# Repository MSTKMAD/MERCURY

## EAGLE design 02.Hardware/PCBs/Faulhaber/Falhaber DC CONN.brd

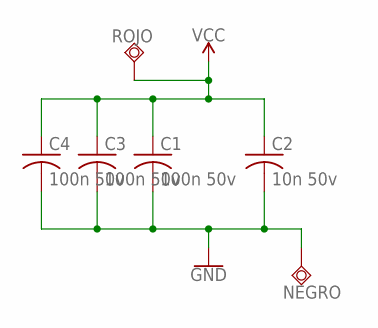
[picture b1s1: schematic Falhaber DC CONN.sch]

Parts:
C1, C3, C4: 100n 50v; C0805
C2: 10n 50v; C0805
NEGRO: TESTPAD_TPSQTP10SQ; TESTPAD_TP10SQ
ROJO: TESTPAD_TPSQTP10SQ; TESTPAD_TP10SQ

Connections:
GND: C1.2, C2.2, C3.2, C4.2, NEGRO.TP
VCC: C1.1, C2.1, C3.1, C4.1, ROJO.TP

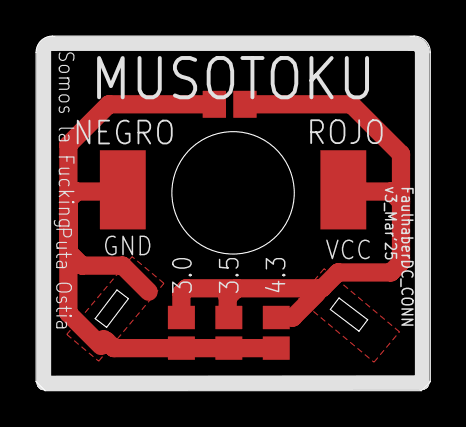
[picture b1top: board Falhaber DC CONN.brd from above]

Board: 2 copper layers, 21.9 x 19.7 mm, 6 parts (0 on the bottom side), 2 nets.

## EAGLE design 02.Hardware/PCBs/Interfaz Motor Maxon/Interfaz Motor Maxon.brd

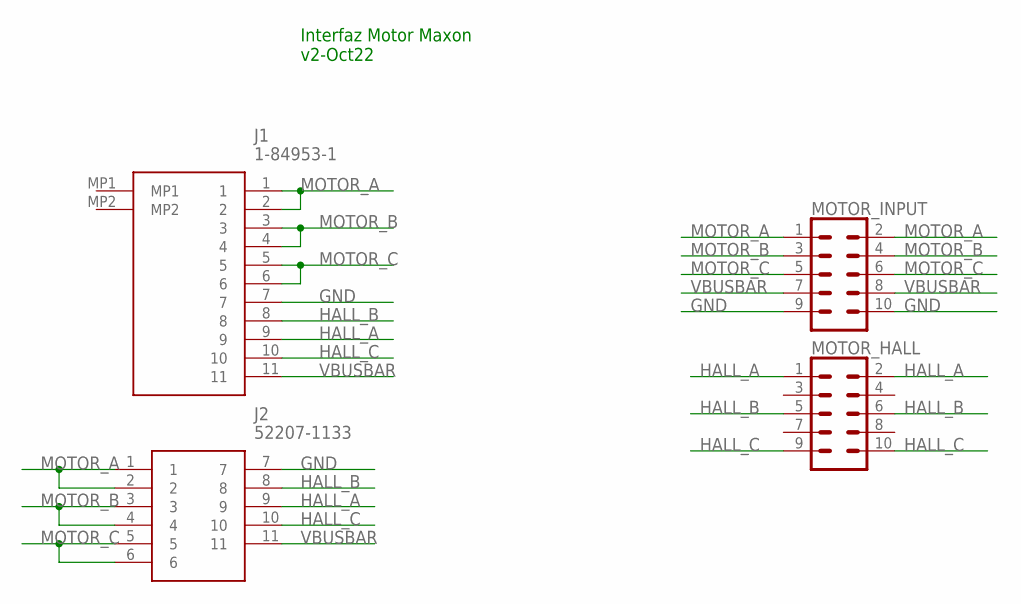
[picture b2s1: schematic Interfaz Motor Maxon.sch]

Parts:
J1: 1-84953-1; 1849531
J2: 52207-1133
MOTOR_HALL: CONN_05X2PTH; 2X5
MOTOR_INPUT: CONN_05X2PTH; 2X5

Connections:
GND: J1.7, J2.7, MOTOR_INPUT.9, MOTOR_INPUT.10
HALL_A: J1.9, J2.9, MOTOR_HALL.1, MOTOR_HALL.2
HALL_B: J1.8, J2.8, MOTOR_HALL.5, MOTOR_HALL.6
HALL_C: J1.10, J2.10, MOTOR_HALL.9, MOTOR_HALL.10
MOTOR_A: J1.1, J1.2, J2.1, J2.2, MOTOR_INPUT.1, MOTOR_INPUT.2
MOTOR_B: J1.3, J1.4, J2.3, J2.4, MOTOR_INPUT.3, MOTOR_INPUT.4
MOTOR_C: J1.5, J1.6, J2.5, J2.6, MOTOR_INPUT.5, MOTOR_INPUT.6
VBUSBAR: J1.11, J2.11, MOTOR_INPUT.7, MOTOR_INPUT.8

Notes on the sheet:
Interfaz Motor Maxon v2-Oct22

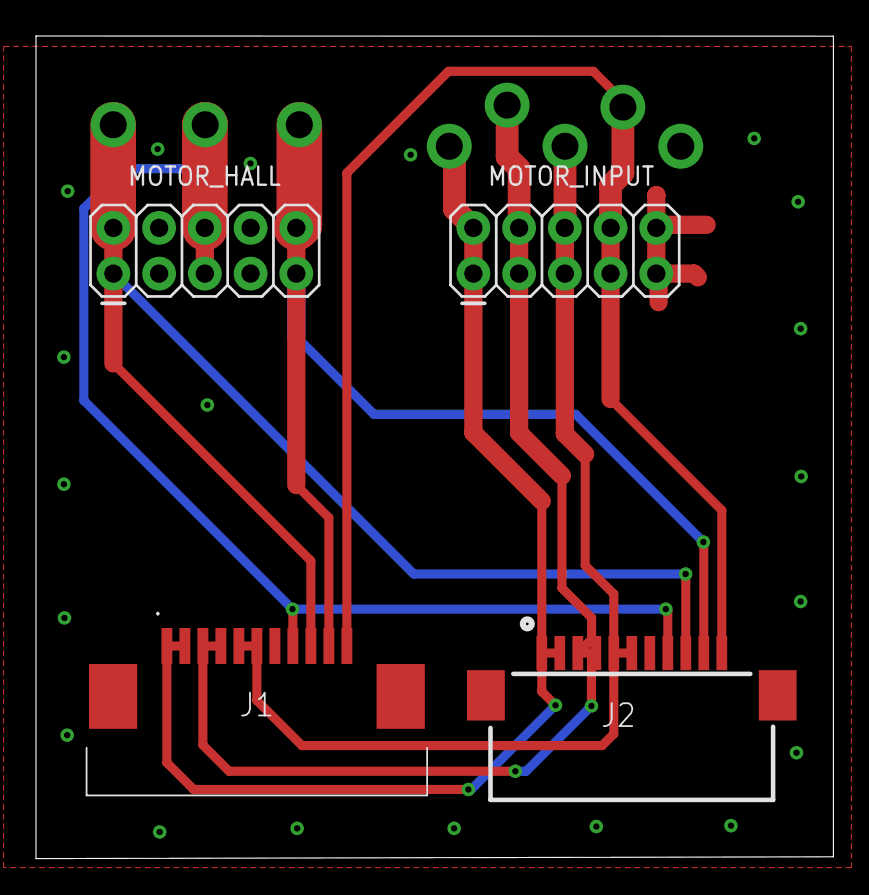
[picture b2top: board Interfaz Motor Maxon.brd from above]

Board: 2 copper layers, 44.3 x 45.7 mm, 4 parts (0 on the bottom side), 8 nets.

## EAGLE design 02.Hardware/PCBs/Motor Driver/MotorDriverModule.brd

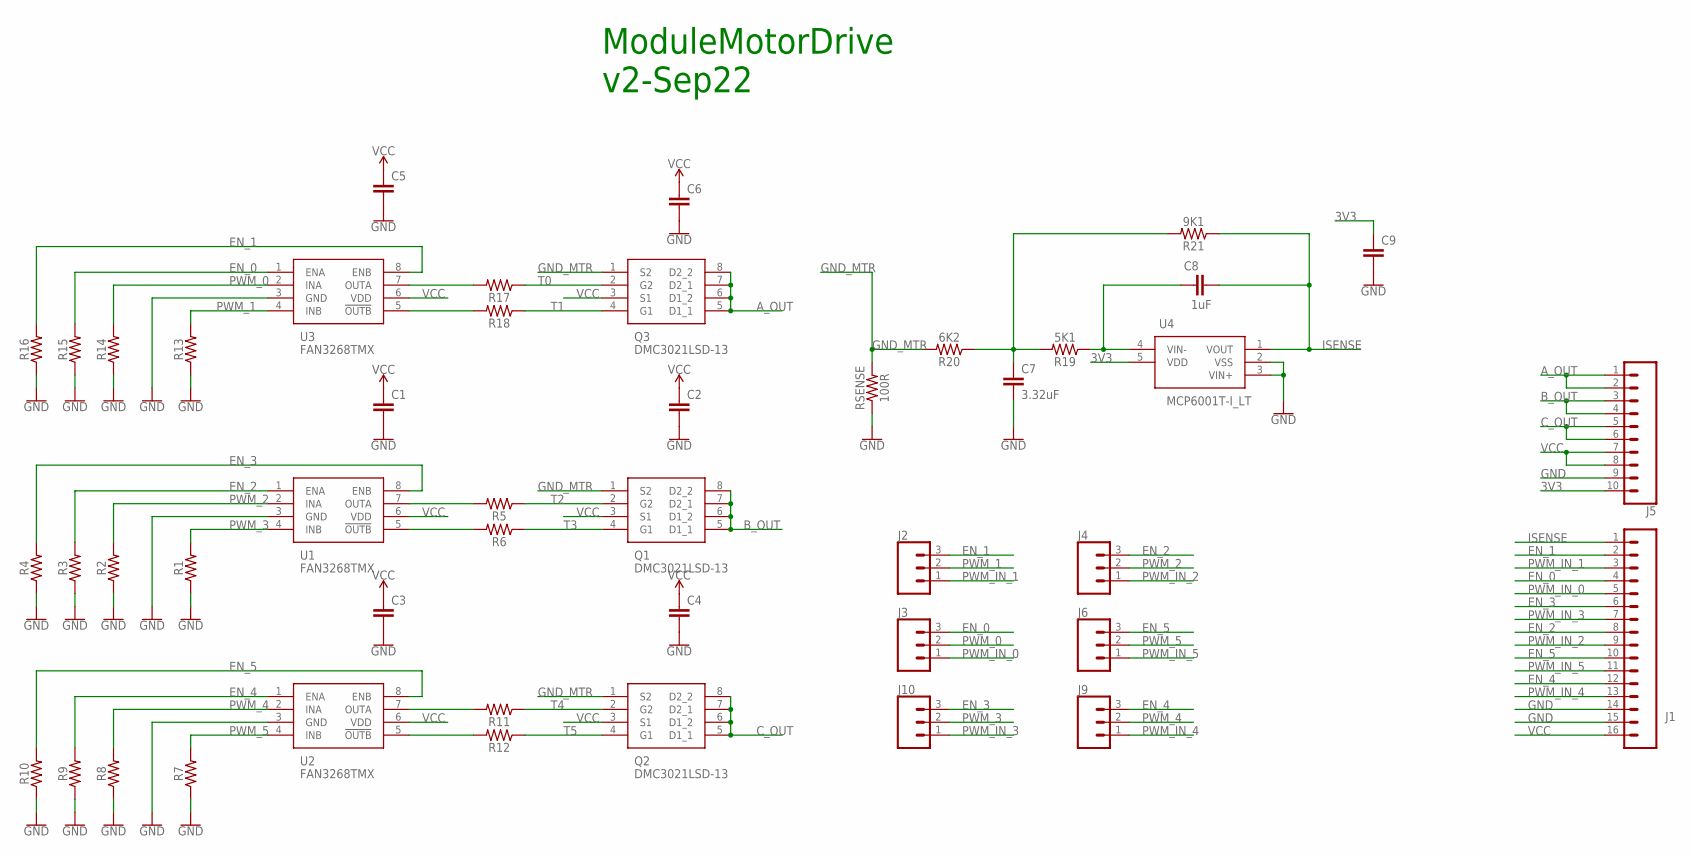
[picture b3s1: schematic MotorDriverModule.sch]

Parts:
C1, C2, C3, C4, C5, C6, C9: C-EUC0805; C0805
C7: 3.32uF; C0805
C8: 1uF; C0805
J1: CONN_16; 1X16
J2, J3, J4, J6, J9, J10: CONN_03; 1X03
J5: CONN_10"; 1X10
Q1, Q2, Q3: DMC3021LSD-13; SOIC127P600X175-8N
R1, R2, R3, R4, R5, R6, R7, R8, R9, R10, R11, R12, R13, R14, R15, R16, R17, R18: 0805
R19: 5K1; 0805
R20: 6K2; 0805
R21: 9K1; 0805
RSENSE: 100R; 1206
U1, U2, U3: FAN3268TMX; SOIC127P600X175-8N
U4: MCP6001T-I_LT; SOT65P210X110-5N

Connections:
3V3: C9.1, J5.10, U4.5 (VDD)
A_OUT: J5.1, J5.2, Q3.5 (D1_1), Q3.6 (D1_2), Q3.7 (D2_1), Q3.8 (D2_2)
B_OUT: J5.3, J5.4, Q1.5 (D1_1), Q1.6 (D1_2), Q1.7 (D2_1), Q1.8 (D2_2)
C_OUT: J5.5, J5.6, Q2.5 (D1_1), Q2.6 (D1_2), Q2.7 (D2_1), Q2.8 (D2_2)
EN_0: J1.4, J3.3, R15.2, U3.1 (ENA)
EN_1: J1.2, J2.3, R16.2, U3.8 (ENB)
EN_2: J1.8, J4.3, R3.2, U1.1 (ENA)
EN_3: J1.6, J10.3, R4.2, U1.8 (ENB)
EN_4: J1.12, J9.3, R9.2, U2.1 (ENA)
EN_5: J1.10, J6.3, R10.2, U2.8 (ENB)
GND: C1.2, C2.2, C3.2, C4.2, C5.2, C6.2, C7.2, C9.2, J1.14, J1.15, J5.9, R1.1, R2.1, R3.1, R4.1, R7.1, R8.1, R9.1, R10.1, R13.1, R14.1, R15.1, R16.1, RSENSE.1, U1.3 (GND), U2.3 (GND), U3.3 (GND), U4.2 (VSS), U4.3 (VIN+)
GND_MTR: Q1.1 (S2), Q2.1 (S2), Q3.1 (S2), R20.2, RSENSE.2
ISENSE: C8.2, J1.1, R21.1, U4.1 (VOUT)
unnamed: C7.1, R19.2, R20.1, R21.2
unnamed: C8.1, R19.1, U4.4 (VIN-)
unnamed: R6.2, U1.5 (!OUTB)
unnamed: R5.2, U1.7 (OUTA)
unnamed: R12.2, U2.5 (!OUTB)
unnamed: R11.2, U2.7 (OUTA)
unnamed: R18.2, U3.5 (!OUTB)
unnamed: R17.2, U3.7 (OUTA)
PWM_0: J3.2, R14.2, U3.2 (INA)
PWM_1: J2.2, R13.2, U3.4 (INB)
PWM_2: J4.2, R2.2, U1.2 (INA)
PWM_3: J10.2, R1.2, U1.4 (INB)
PWM_4: J9.2, R8.2, U2.2 (INA)
PWM_5: J6.2, R7.2, U2.4 (INB)
PWM_IN_0: J1.5, J3.1
PWM_IN_1: J1.3, J2.1
PWM_IN_2: J1.9, J4.1
PWM_IN_3: J1.7, J10.1
PWM_IN_4: J1.13, J9.1
PWM_IN_5: J1.11, J6.1
T0: Q3.2 (G2), R17.1
T1: Q3.4 (G1), R18.1
T2: Q1.2 (G2), R5.1
T3: Q1.4 (G1), R6.1
T4: Q2.2 (G2), R11.1
T5: Q2.4 (G1), R12.1
VCC: C1.1, C2.1, C3.1, C4.1, C5.1, C6.1, J1.16, J5.7, J5.8, Q1.3 (S1), Q2.3 (S1), Q3.3 (S1), U1.6 (VDD), U2.6 (VDD), U3.6 (VDD)

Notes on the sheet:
ModuleMotorDrive v2-Sep22

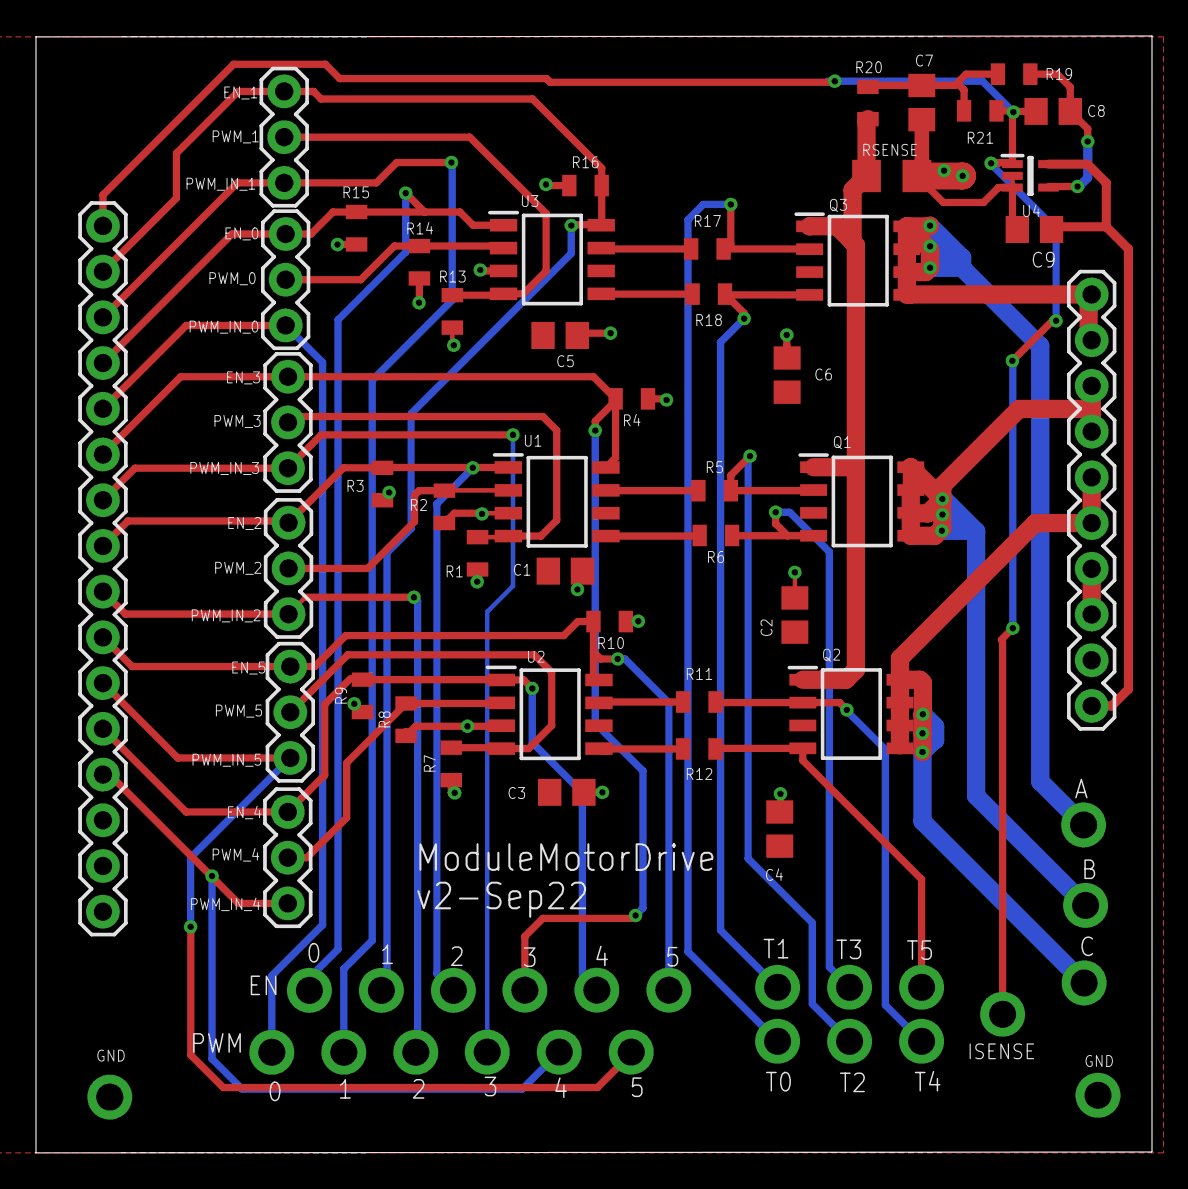
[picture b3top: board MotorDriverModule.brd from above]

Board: 2 copper layers, 62.0 x 62.0 mm, 46 parts (0 on the bottom side), 40 nets.

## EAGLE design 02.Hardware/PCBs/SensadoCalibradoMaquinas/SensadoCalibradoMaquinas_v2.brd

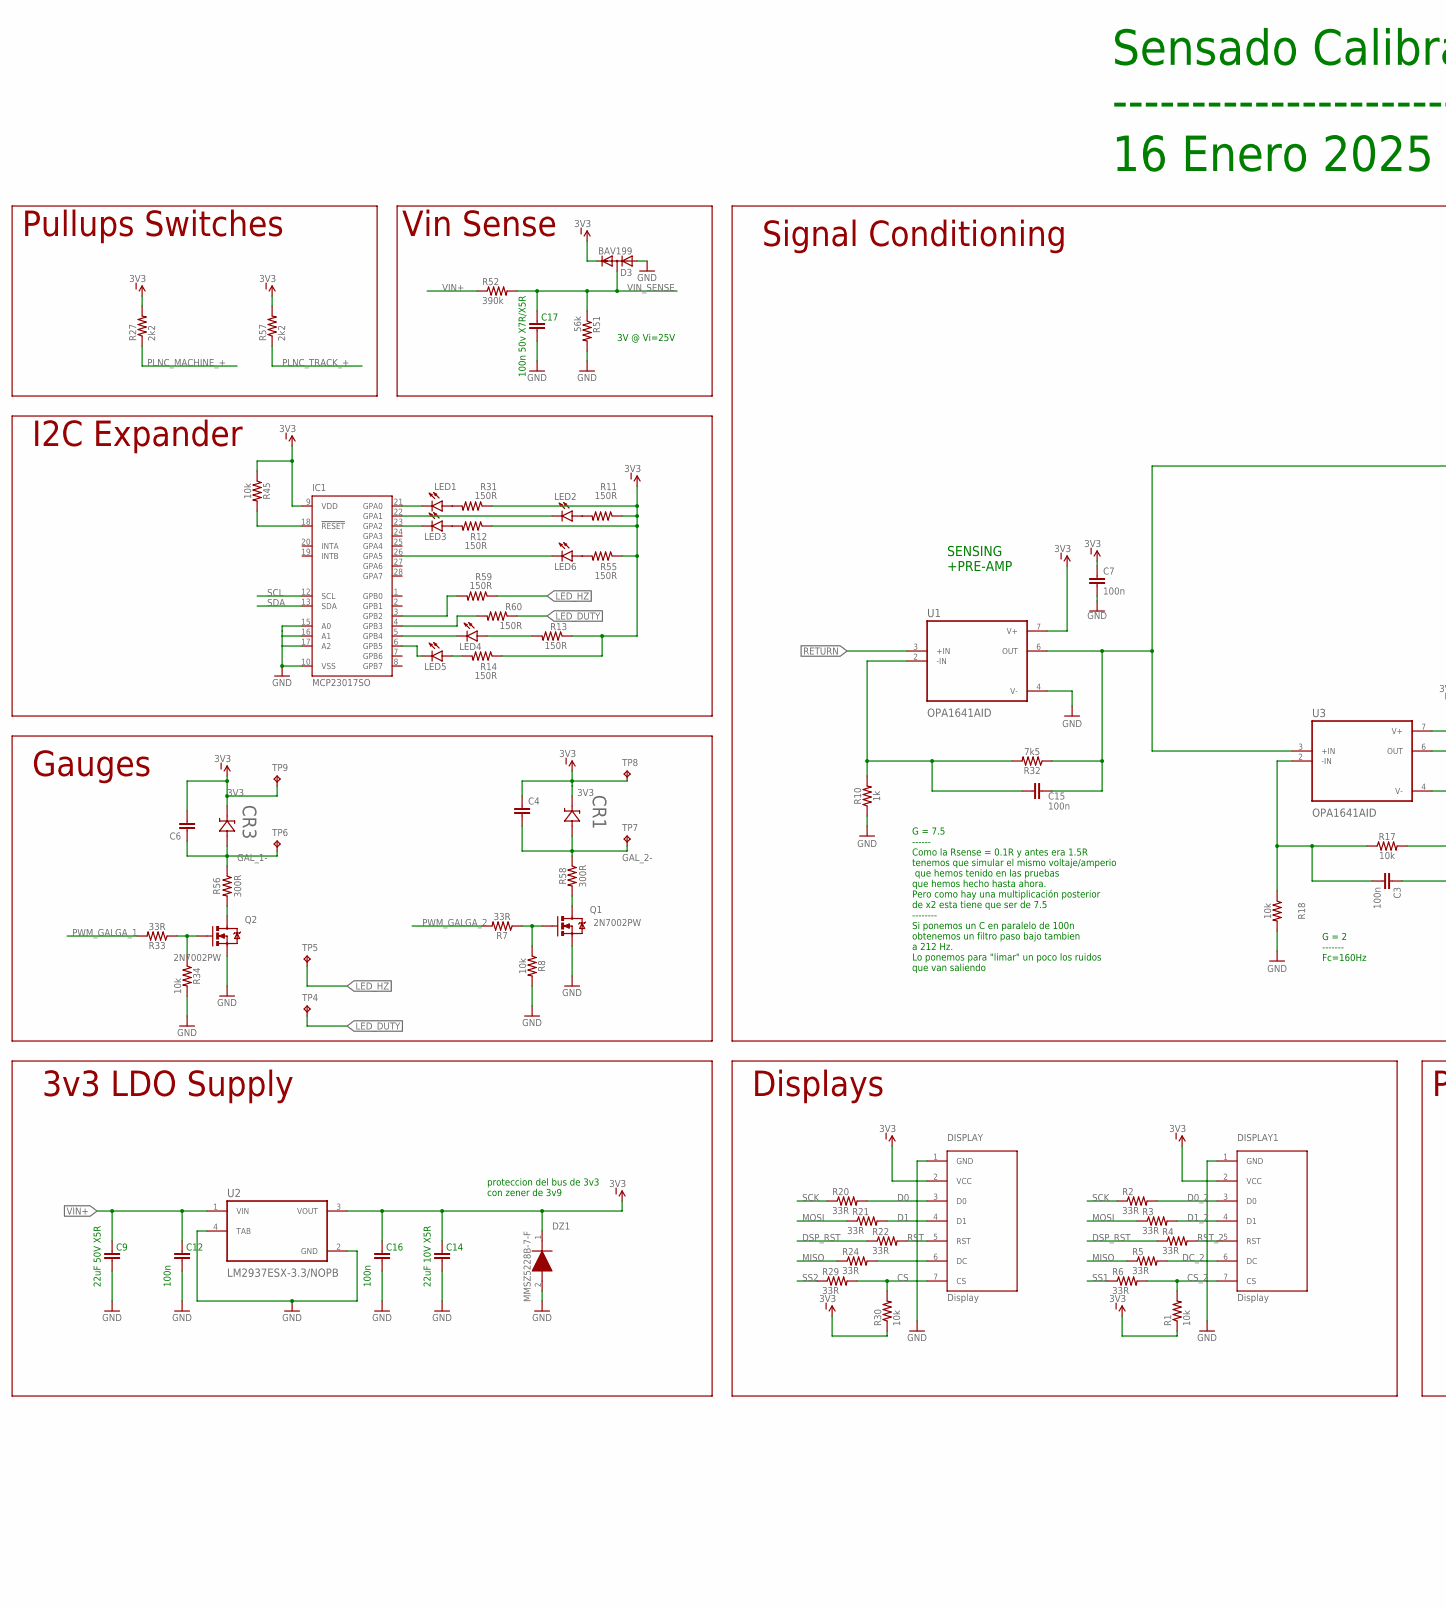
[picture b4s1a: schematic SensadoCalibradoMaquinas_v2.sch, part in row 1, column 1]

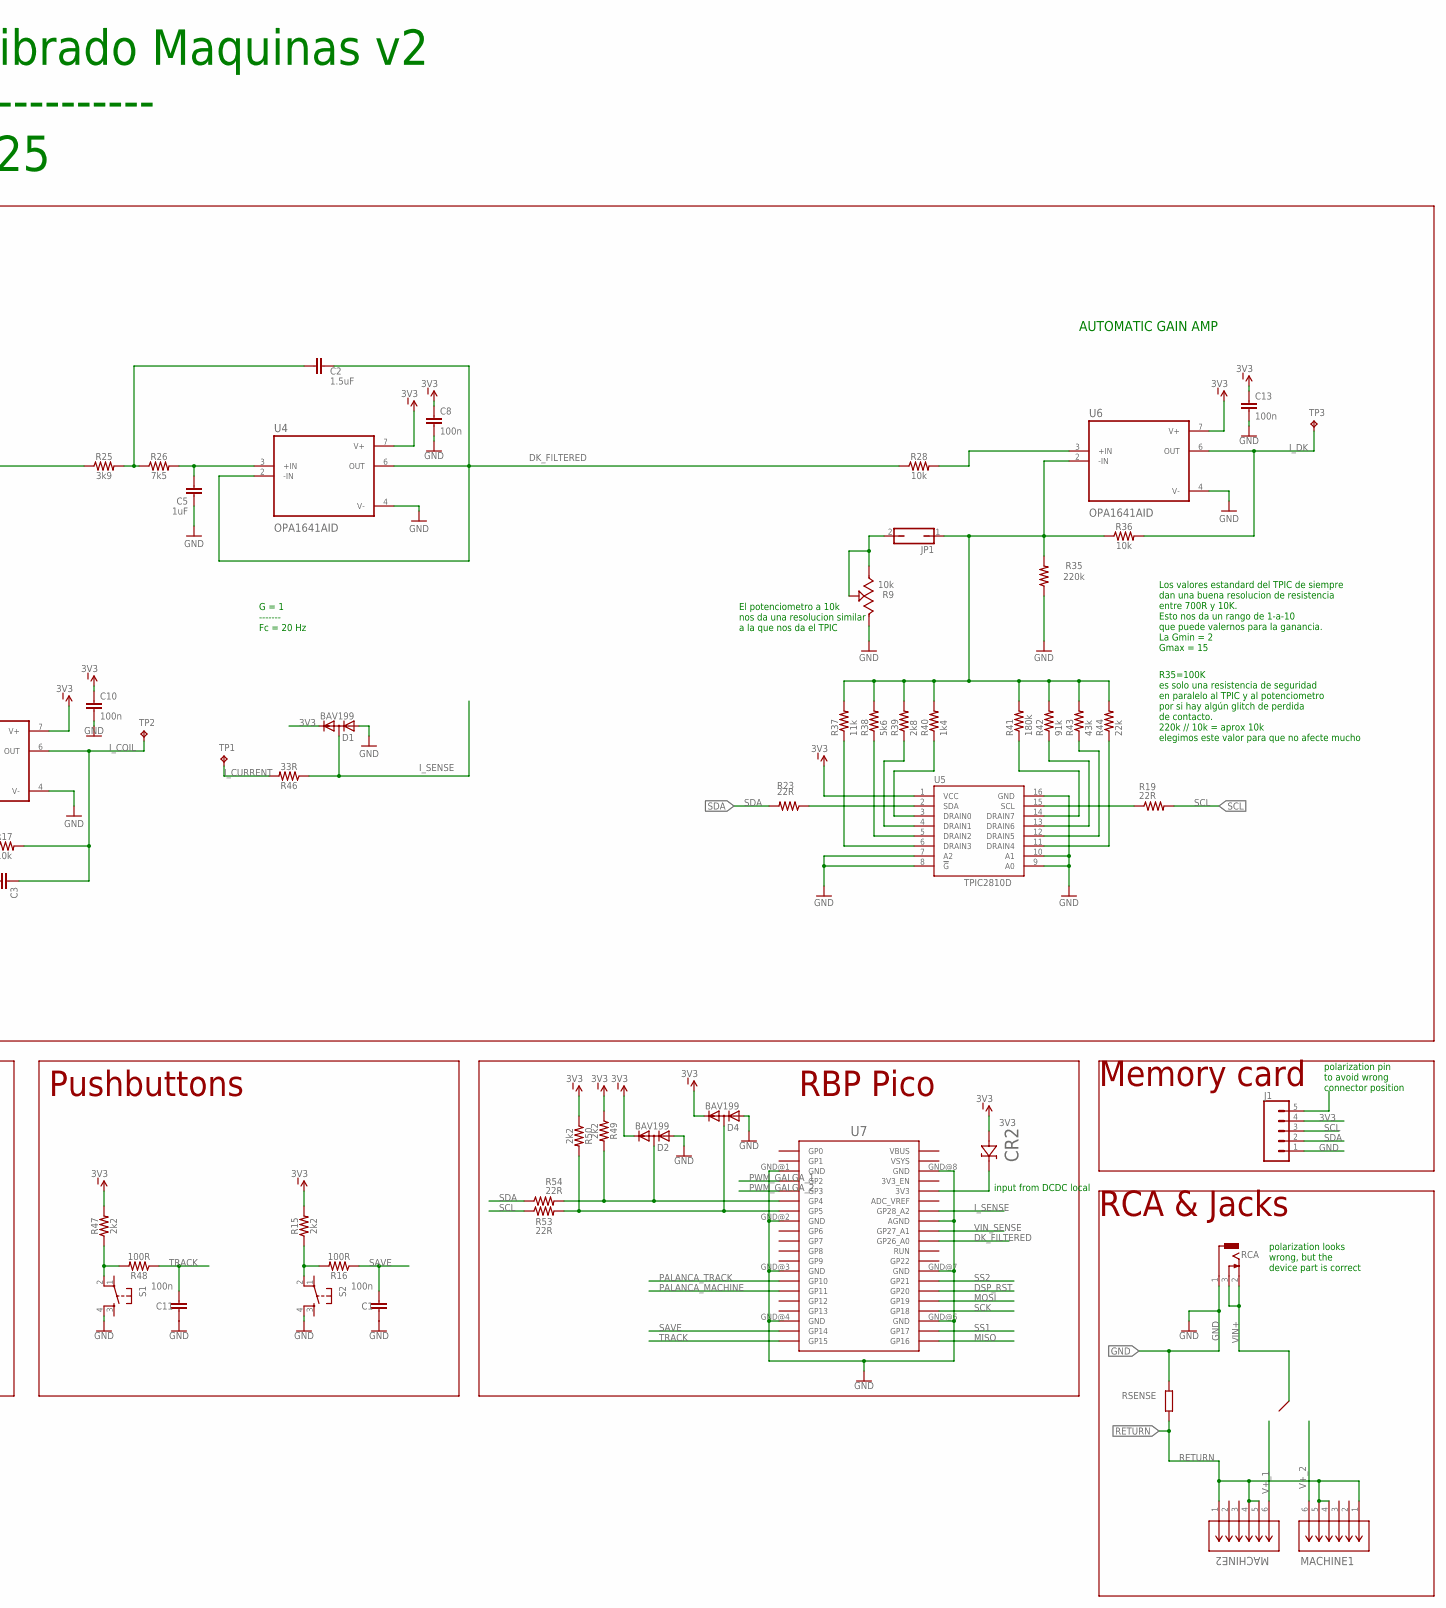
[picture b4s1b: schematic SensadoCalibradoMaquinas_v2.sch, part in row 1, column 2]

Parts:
C1, C3, C7, C8, C10, C11, C12, C13, C15, C16: 100n; 0805
C2: 1.5uF; 0805
C4, C6: CAP0805; 0805
C5: 1uF; 0805
C9: 22uF 50V X5R; 0805
C14: 22uF 10V X5R; 0805
C17: 100n 50v X7R/X5R; 0805
CR1, CR2, CR3: STPS1L40U; SMB_STM
D1, D2, D3, D4: BAV199; SOT23
DISPLAY, DISPLAY1: Display; OLED_LCD
DZ1: MMSZ5228B-7-F; SODFL3518X115N
IC1: MCP23017SO; SO28W
J1: CONN_05; 1X05
JP1: JP1Q; JP1
LED1, LED2, LED3, LED4, LED5, LED6: LED3MM
MACHINE1, MACHINE2: ACJS-MHDR; CONN_MHDR_AMP
Q1, Q2: 2N7002PW; SOT323
R1, R8, R17, R18, R28, R30, R34, R36, R45: 10k; 0805
R2, R3, R4, R5, R6, R7, R20, R21, R22, R24, R29, R33, R46: 33R; 0805
R9: 10k; TRIM_PT01-D120D-B104
R10: 1k; 0805
R11, R12, R13, R14, R31, R55, R59, R60: 150R; 0805
R15, R27, R47, R49, R50, R57: 2k2; 0805
R16, R48: 100R; 0805
R19, R23, R53, R54: 22R; 0805
R25: 3k9; 0805
R26, R32: 7k5; 0805
R35: 220k; 0805
R37: 11k; 0805
R38: 5k6; 0805
R39: 2k8; 0805
R40: 1k4; 0805
R41: 180k; 0805
R42: 91k; 0805
R43: 43k; 0805
R44: 22k; 0805
R51: 56k; 0805
R52: 390k; 0805
R56, R58: 300R; 0805
RCA: PJRAN1X1U01X
RSENSE: 0.1R; RESC6332X71
S1, S2: TAC_SWITCH_KSC931G-SMD; TAC_SW_SMD_KSC931G
TP1, TP2, TP3, TP4, TP5, TP6, TP7, TP8, TP9: TPTP06SQ; TP06SQ
U1, U3, U4, U6: OPA1641AID; SOIC127P599X175-8N
U2: LM2937ESX-3.3/NOPB; TO254P1524X483-4N
U5: TPIC2810D; SO16
U7: RPI_PICO_IG-TH; RPI_PICO_TH

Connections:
3V3: C4.1, C6.2, C7.2, C8.2, C10.2, C13.2, C14.2, C16.2, CR1.2, CR2.1, CR3.2, D1.2 (C), D2.2 (C), D3.2 (C), D4.2 (C), DISPLAY.2 (VCC), DISPLAY1.2 (VCC), DZ1.1 (K), IC1.9 (VDD), J1.4, R1.1, R11.1, R12.1, R13.1, R14.1, R15.2, R27.2, R30.1, R31.1, R45.1, R47.2, R49.1, R50.1, R55.1, R57.2, TP8.TP, TP9.TP, U1.7 (V+), U2.3 (VOUT), U3.7 (V+), U4.7 (V+), U5.1 (VCC), U6.7 (V+)
CS: DISPLAY.7 (CS), R29.2, R30.2
CS_2: DISPLAY1.7 (CS), R1.2, R6.2
D0: DISPLAY.3 (D0), R20.2
D0_2: DISPLAY1.3 (D0), R2.2
D1: DISPLAY.4 (D1), R21.2
D1_2: DISPLAY1.4 (D1), R3.2
DC_2: DISPLAY1.6 (DC), R5.2
DK_FILTERED: C2.1, R28.1, U4.2 (-IN), U4.6 (OUT), U7.GP26_A0
DSP_RST: R4.1, R22.1, U7.GP20
GAIN: C15.1, R25.1, R32.1, U1.6 (OUT), U3.3 (+IN)
GAL_1-: C6.1, CR3.1, R56.1, TP6.TP
GAL_2-: C4.2, CR1.1, R58.1, TP7.TP
GND: C1.1, C5.1, C7.1, C8.1, C9.1, C10.1, C11.1, C12.1, C13.1, C14.1, C16.1, C17.1, D1.1 (A), D2.1 (A), D3.1 (A), D4.1 (A), DISPLAY.1 (GND), DISPLAY1.1 (GND), DZ1.2 (A), IC1.10 (VSS), IC1.15 (A0), IC1.16 (A1), IC1.17 (A2), J1.1, Q1.2 (S), Q2.2 (S), R8.2, R9.1, R10.1, R18.2, R34.2, R35.1, R51.2, RCA.1, RSENSE.2, S1.4, S2.4, U1.4 (V-), U2.2 (GND), U2.4 (TAB), U3.4 (V-), U4.4 (V-), U5.7 (A2), U5.8 (!G), U5.9 (A0), U5.10 (A1), U5.16 (GND), U6.4 (V-), U7.AGND, U7.GND@1 (GND), U7.GND@2 (GND), U7.GND@3 (GND), U7.GND@4 (GND), U7.GND@6 (GND), U7.GND@7 (GND), U7.GND@8 (GND)
I_COIL: C3.1, R17.2, TP2.TP, U3.6 (OUT)
I_CURRENT: R46.2, TP1.TP
I_DK: R36.2, TP3.TP, U6.6 (OUT)
I_SENSE: D1.3 (AC), R46.1, U7.GP28_A2
LED_DUTY: R60.1, TP4.TP
LED_HZ: R59.1, TP5.TP
MISO: R5.1, R24.1, U7.GP16
MOSI: R3.1, R21.1, U7.GP19
unnamed: D2.3 (AC), R49.2, R54.2, U7.GP4
unnamed: Q2.1 (G), R33.1, R34.1
unnamed: Q1.1 (G), R7.1, R8.1
unnamed: C15.2, R10.2, R32.2, U1.2 (-IN)
unnamed: R28.2, U6.3 (+IN)
unnamed: LED1.A, R31.2
unnamed: DISPLAY.6 (DC), R24.2
unnamed: IC1.22 (GPA1), LED2.K (C)
unnamed: LED2.A, R11.2
unnamed: IC1.23 (GPA2), LED3.K (C)
unnamed: LED4.A, R13.2
unnamed: IC1.5 (GPB4), LED4.K (C)
unnamed: LED5.A, R14.2
unnamed: IC1.6 (GPB5), LED5.K (C)
unnamed: R15.1, R16.2, S2.2
unnamed: JP1.1, R35.2, R36.1, R37.2, R38.2, R39.2, R40.2, R41.2, R42.2, R43.2, R44.2, U6.2 (-IN)
unnamed: R37.1, U5.6 (DRAIN3)
unnamed: R38.1, U5.5 (DRAIN2)
unnamed: R39.1, U5.4 (DRAIN1)
unnamed: R40.1, U5.3 (DRAIN0)
unnamed: R41.1, U5.14 (DRAIN7)
unnamed: R42.1, U5.13 (DRAIN6)
unnamed: R43.1, U5.12 (DRAIN5)
unnamed: R44.1, U5.11 (DRAIN4)
unnamed: IC1.3 (GPB2), R59.2
unnamed: R19.1, U5.15 (SCL)
unnamed: IC1.4 (GPB3), R60.2
unnamed: LED6.A, R55.2
unnamed: CR2.2, U7.3V3
unnamed: C2.2, R25.2, R26.1
unnamed: C5.2, R26.2, U4.3 (+IN)
unnamed: C3.2, R17.1, R18.1, U3.2 (-IN)
unnamed: D4.3 (AC), R50.2, R53.2, U7.GP5
unnamed: IC1.26 (GPA5), LED6.K (C)
unnamed: R47.1, R48.2, S1.2
unnamed: R23.1, U5.2 (SDA)
unnamed: Q2.3 (D), R56.2
unnamed: LED3.A, R12.2
unnamed: Q1.3 (D), R58.2
unnamed: IC1.18 (!RESET), R45.2
unnamed: JP1.2, R9.2, R9.3
unnamed: IC1.21 (GPA0), LED1.K (C)
PALANCA_MACHINE: U7.GP11
PALANCA_TRACK: U7.GP10
PLNC_MACHINE_+: R27.1
PLNC_TRACK_+: R57.1
PWM_GALGA_1: R33.2, U7.GP2
PWM_GALGA_2: R7.2, U7.GP3
RETURN: MACHINE1.1, MACHINE1.4, MACHINE1.5, MACHINE2.1, MACHINE2.4, MACHINE2.5, RSENSE.1, U1.3 (+IN)
RST: DISPLAY.5 (RST), R22.2
RST_2: DISPLAY1.5 (RST), R4.2
SAVE: C1.2, R16.1, U7.GP14
SCK: R2.1, R20.1, U7.GP18
SCL: IC1.12 (SCL), J1.3, R19.2, R53.1
SDA: IC1.13 (SDA), J1.2, R23.2, R54.1
SS1: R6.1, U7.GP17
SS2: R29.1, U7.GP21
TRACK: C11.2, R48.1, U7.GP15
V+_1: MACHINE2.6
V+_2: MACHINE1.6
VIN+: C9.2, C12.2, R52.1, RCA.2, RCA.3, U2.1 (VIN)
VIN_SENSE: C17.2, D3.3 (AC), R51.1, R52.2, U7.GP27_A1

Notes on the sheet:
3v3 LDO Supply
proteccion del bus de 3v3 con zener de 3v9
3V @ Vi=25V
input from DCDC local
polarization pin to avoid wrong connector position
polarization looks wrong, but the device part is correct
SENSING +PRE-AMP
AUTOMATIC GAIN AMP
G = 7.5 ------ Como la Rsense = 0.1R y antes era 1.5R tenemos que simular el mismo voltaje/amperio que hemos tenido en las pruebas que hemos hecho hasta ahora. Pero como hay una multiplicación posterior de x2 esta tiene que ser de 7.5 -------- Si ponemos un C en paralelo de 100n obtenemos un filtro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
G = 2 ------- Fc=160Hz
G = 1 ------- Fc = 20 Hz
Los valores estandard del TPIC de siempre dan una buena resolucion de resistencia entre 700R y 10K. Esto nos da un rango de 1-a-10 que puede valernos para la ganancia. La Gmin = 2 Gmax = 15
El potenciometro a 10k nos da una resolucion similar a la que nos da el TPIC
R35=100K es solo una resistencia de seguridad en paralelo al TPIC y al potenciometro por si hay algún glitch de perdida de contacto. 220k // 10k = aprox 10k elegimos este valor para que no afecte mucho
Sensado Calibrado Maquinas v2 --------------------------- 16 Enero 2025
Displays
Gauges
Pushbuttons
Signal Conditioning
I2C Expander
RCA & Jacks
Memory card
RBP Pico
Pullups Switches
Vin Sense

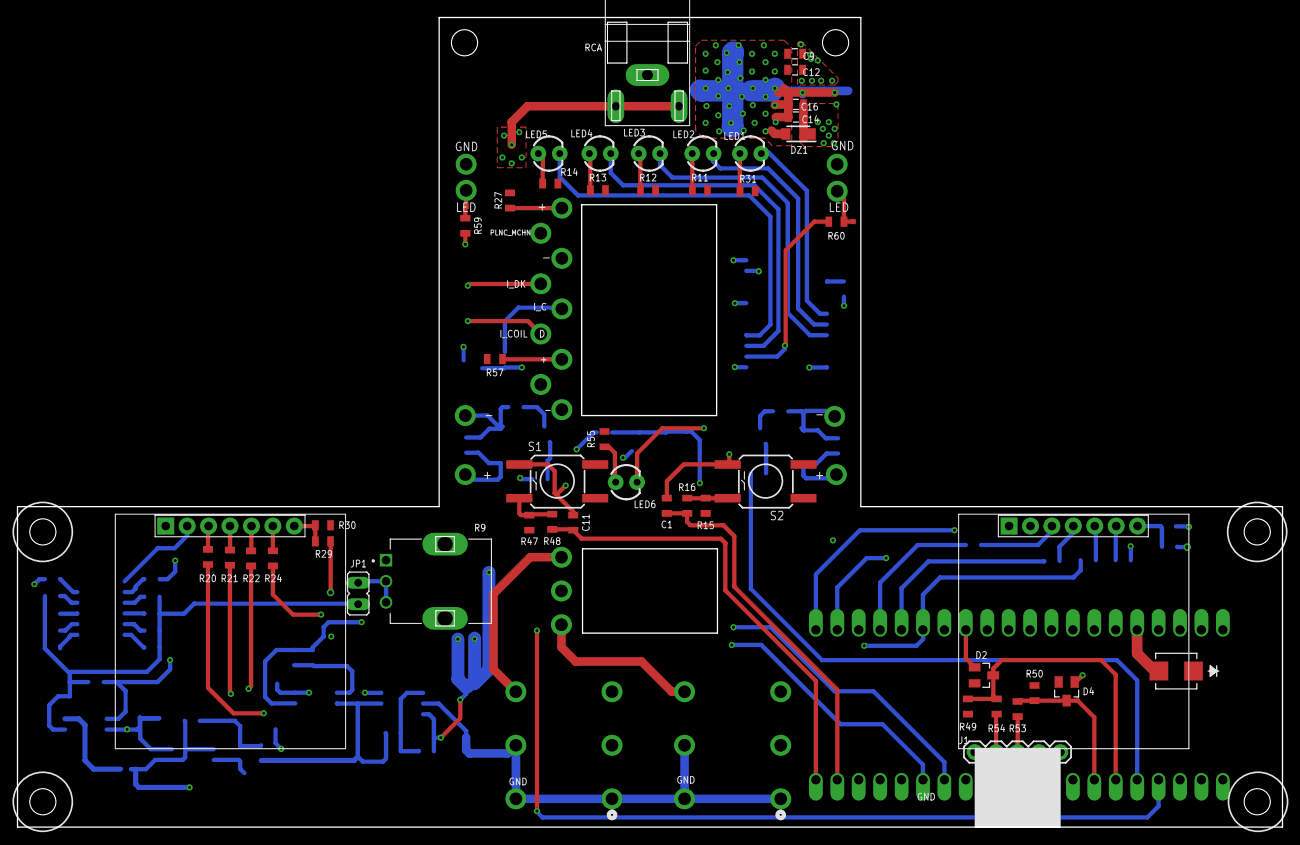
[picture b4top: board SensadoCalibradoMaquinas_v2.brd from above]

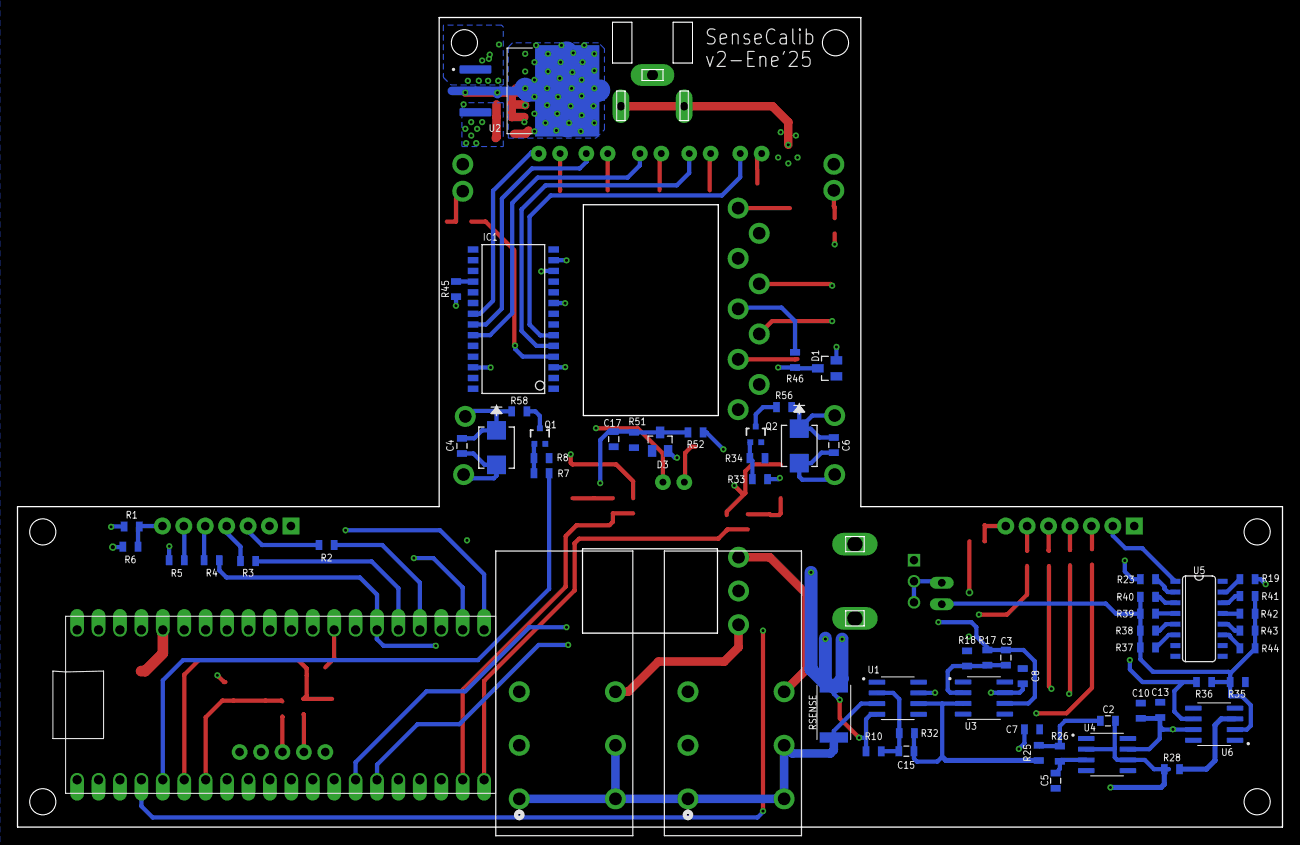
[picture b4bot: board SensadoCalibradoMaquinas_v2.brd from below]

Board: 4 copper layers, 150.0 x 96.0 mm, 120 parts (64 on the bottom side), 78 nets.

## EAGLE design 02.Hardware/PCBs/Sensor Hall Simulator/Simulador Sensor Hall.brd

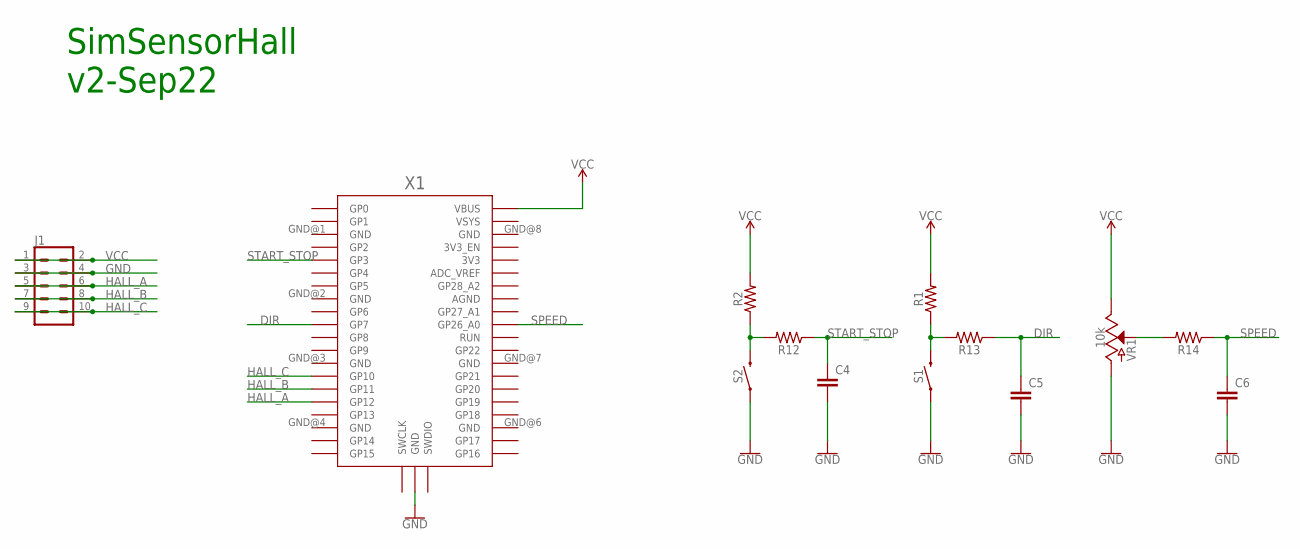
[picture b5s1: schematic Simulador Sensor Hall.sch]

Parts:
C4, C5, C6: C-EUC0805K; C0805K
J1: CONN_05X2PTH; 2X5
R1, R2, R12, R13, R14: 0805
S1, S2: MOMENTARY-SWITCH-SPST-SMD-6.2MM-TALL; TACTILE_SWITCH_SMD_6.2MM_TALL
VR1: 10k; POT-PTH-ALPS
X1: RPI_PICO_IG-TH; RPI_PICO_TH

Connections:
DIR: C5.1, R13.1, X1.GP7
GND: C4.2, C5.2, C6.2, J1.3, J1.4, S1.A2 (1), S2.A2 (1), VR1.P$3 (A), X1.GND@5 (GND)
HALL_A: J1.5, J1.6, X1.GP12
HALL_B: J1.7, J1.8, X1.GP11
HALL_C: J1.9, J1.10, X1.GP10
unnamed: R2.1, R12.2, S2.B2 (2)
unnamed: R1.1, R13.2, S1.B2 (2)
unnamed: R14.2, VR1.P$2 (S)
SPEED: C6.1, R14.1, X1.GP26_A0
START_STOP: C4.1, R12.1, X1.GP3
VCC: J1.1, J1.2, R1.2, R2.2, VR1.P$1 (E), X1.VBUS

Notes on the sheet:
SimSensorHall v2-Sep22

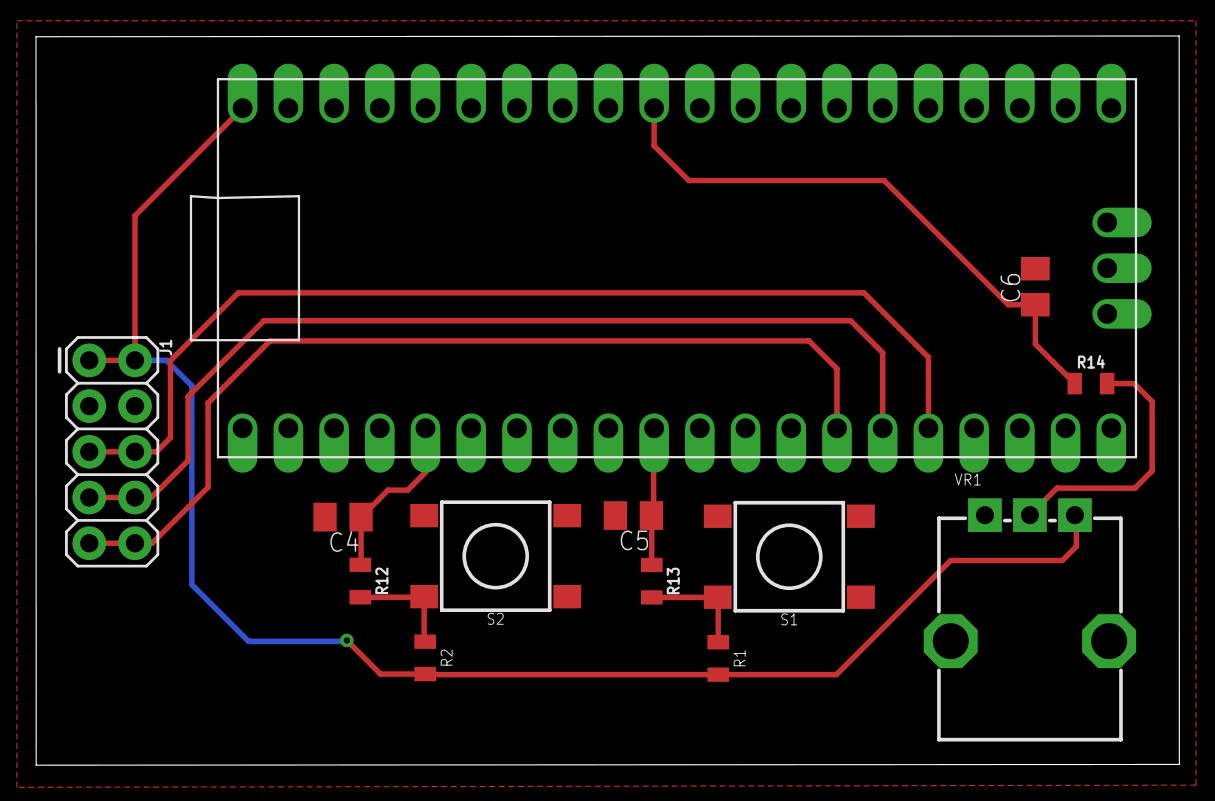
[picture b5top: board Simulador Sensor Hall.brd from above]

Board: 2 copper layers, 63.5 x 40.5 mm, 13 parts (0 on the bottom side), 11 nets.

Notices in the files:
parts and their libraries:
SparkFun-Resistors: Licensing: Creative Commons ShareAlike 4.0 International - https://creativecommons.org/licenses/by-sa/4.0
SparkFun-DiscreteSemi: Licensing: CC v3.0 Share-Alike You are welcome to use this library for commercial purposes.
